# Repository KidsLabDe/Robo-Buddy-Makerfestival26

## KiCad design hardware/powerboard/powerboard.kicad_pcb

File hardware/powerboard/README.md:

# Powerboard (KiCad)

Trägerplatine, die den Robo-Buddy akkubetrieben macht. Anforderungen und Begründungen: `POWERBOARD-HANDOFF.md` im Repo-Hauptordner. ESP-Board: `../esp32-c6-zero/`.

Stand Rev 0.2: **Schaltplan fertig, ERC ohne Meldungen. Platine mit echter Kontur, platziert und geroutet (2 Lagen). Fertigungsdateien für JLCPCB in `fertigung/`. Rev 0.2 ist bestellt, siehe „Bestellung“.**

## Was drauf ist

- Akku (Pouch-LiPo, 1S) an J1, JST-PH **THT**: Verpolschutz (2 × AO3401A parallel), Zellschutz DW01A mit 2 × FS8205A parallel (Auslösung ~6–8 A).
- Strom- und Spannungsmessung: INA226 an I²C (Adresse 0x45), Shunt 10 mΩ zwischen `BAT_CELL` und `BAT+`. Misst Lade- (negativ) und Entladestrom sowie die Akkuspannung.
- Lader TP4056, 235 mA, aus dem 5V-Pin des ESP (USB). Rote LED leuchtet nur beim Laden.
- Ein/Aus (Q5 + SW1) und ideale Diode LM66100 für den ESP.
- 5-V-Servoschiene: Boost TPS61023 (≥ 2 A bei 5 V), von GPIO15 geschaltet. Bei EN low ist der Ausgang echt vom Akku getrennt.
- Ports (alle 2,54 mm, THT-Kit):

| Port | Belegung | GPIO |
|---|---|---|
| Servo 1–4 (J2, J3, J5, J6) | S + − (5 V) | 19, 18, 16, 17 |
| Analog A0–A2 (J7–J9) | GND 3V3 SIG, 1 kΩ in Serie, 0–3,1 V | 0, 1, 2 |
| I²C 1, 2 (J10, J11) | GND 3V3 SDA SCL, 4,7 kΩ Pull-ups | SDA 14, SCL 22 |
| Display (J4) | VCC GND SCL SDA DC CS RST, per Kabel | 4, 5, 20, 21, 3 |

## Platine

`powerboard.kicad_pcb` erzeugt `tools/gen_pcb.py`. Kontur, Platzierung und Herleitung der Maße stehen dort im Kopf.

**Kontur** aus `cad/MF26-Roboter.step`: Innenseite der Hülle direkt über der Bodenplatte, 0,5 mm Luft. Ca. 55 × 53 mm, vorne gerade hinter dem Display, hinten zwei Schrägen und ein gerades Stück vor dem Dom des Schleifrads.

**Platzierung:**
- ESP an der einen hinteren Schräge, USB-C zeigt durch die Wand. Schalter und Lade-LED an der anderen Schräge.
- Servo-Leisten an der einen Längsseite, Analog-Leisten an der anderen, beide ein Stück vom Rand nach innen gesetzt (die Kabel kommen von oben).
- **Leistungsblock vorne**, alles mit festem, breitem Kupfer vorverdrahtet (`POWER_TRACKS` in `gen_pcb.py`):
  - 5-V-Schiene (1,2 mm) direkt hinter den Servo-Leisten, Stich zu jedem Plus-Pin
  - Boost TPS61023 nach dem Layout-Beispiel von TI: Spule direkt über dem SW-Pin, vier Ausgangskondensatoren in einer Spalte zwischen VOUT und GND, Eingangskondensator an VIN
  - Akkupfad J1 → Verpolschutz (Q1, Q7) → Shunt R15 → Spule, Zellschutz Q2/Q6 neben J1
- Display-Leiste J4 ungefähr mittig auf der Displayachse, hinter dem Leistungsblock; zum Display per Kabel.
- I²C-Leisten, Testpunkte und Pull-ups in der Mitte, INA226 hinter dem Shunt.
- Lader und Power Path beim ESP, Ein/Aus-FET direkt hinter dem Schalter.

| Ansicht | Datei |
|---|---|
| Passung im Gehäuse (Schnitte) | `ansichten/passung_schnitte.png`, erzeugt von `tools/render_fit.py` |
| 2D oben / unten | `ansichten/2d_oben.png`, `ansichten/2d_unten.png` |
| 3D oben / unten / schräg | `ansichten/3d_oben.png`, `ansichten/3d_unten.png`, `ansichten/3d_schraeg.png` |

Hinweise:
- **USB-C** endet ca. 1,25 mm hinter der Außenfläche der Hülle. Ganz bündig ginge nur, wenn das ESP-Modul 1 mm über die Platinenkante ragt. Dann läge aber Pad 1 auf der Kante, weil der erste Pin nur 1,6 mm hinter der Modulkante sitzt. Bei Bedarf lässt sich die Wand um die Buchse innen etwas ausdünnen.
- **Display:** Es steht vorne tiefer als die Platine. J4 ist deshalb eine Stiftleiste für ein kurzes Kabel.
- Mindestabstand im Projekt 0,15 mm, minimale Bahnbreite 0,15 mm (Pads des SOT-563 und des INA226 liegen so eng). JLC fertigt 0,1 mm.
- **Drehung bei JLC:** Die Bauteilmodelle von JLC liegen teils anders als die KiCad-Footprints. `tools/export_jlc.py` korrigiert die Drehung in der CPL pro LCSC-Teil (`JLC_ROTATION`): AO3401A, FS8205A, TPS61023 um 180°, DW01A, LM66100, TP4056, INA226 um 90° im Uhrzeigersinn. Am 8. Oktober 2026 im Platzierungs-Viewer von JLC geprüft, Pin 1 jedes Teils sitzt auf der Pin-1-Markierung, D1 mit Kathode an Pin 1. Neue Teile dort prüfen und eintragen.
- Bauteilnummern stehen nicht im Bestückungsdruck, nur auf der Fab-Lage (Bestückung bei JLC geht nach Koordinaten, die Anschlüsse haben eigene Beschriftungen).
- In 3D fehlt das ESP-Modul selbst, weil es dafür kein 3D-Modell gibt. Zu sehen sind nur die beiden Buchsenleisten.

### Öffnungen in der Hülle (CAD-Koordinaten, für FreeCAD)

Platine liegt auf der Bodenplatte, Unterseite z = 12,5, Oberseite z = 14,1.

| Öffnung | Wand | Mitte (x, y) an der Wandaußenseite | Höhe z | Hinweis |
|---|---|---|---|---|
| USB-C | Schräge, niedriges y | (42,2 / 5,2) | ≈ 27–28 | hängt von Leisten- und Modulhöhe ab, am Muster messen; Öffnung für den Stecker ~12,5 × 7 mm |
| Schalterhebel | Schräge, hohes y | (47,6 / 41,7) | ≈ 15,5 | Hebel ragt ~1,4 mm aus der Wand, 2 mm Hub entlang der Wand |
| Lade-LED | Schräge, hohes y | (38,0 / 48,9) | ≈ 14,5 | 0603 strahlt nach oben, sitzt 1 mm vor der Wand: Fenster knapp über der Platine oder Lichtleiter |

## Dateien

| Datei | Inhalt |
|---|---|
| `powerboard.kicad_sch` | Schaltplan, **erzeugt** von `tools/gen_sch.py` |
| `powerboard.kicad_sym` | Projektsymbole FS8205A, TPS61023 und ESP32-C6-Zero, erzeugt von `tools/gen_lib.py` |
| `powerboard.pretty/` | Footprints C6-Zero-Sockel, Shunt mit Kelvin-Pads, Schalter mit runden Pads, KidsLab-Logo; erzeugt von `tools/gen_lib.py` |
| `logo/kidslab-logo.svg` | Vorlage für das Logo auf der Unterseite |
| `powerboard.kicad_pcb` | Platine: Platzierung von `tools/gen_pcb.py`, Leiterbahnen von `tools/route.py` |
| `fertigung/` | JLCPCB: `powerboard_gerber.zip`, `powerboard_bom.csv`, `powerboard_cpl.csv`, erzeugt von `tools/export_jlc.py` |
| `tools/` | Generatoren, Routing (`route.py`, `maze.py`), Ansichten (`render_views.py`, `render_fit.py`) |

Schaltplan und Platine entstehen aus den Skripten. Änderungen also dort machen und neu erzeugen, nicht im Editor:

```
python3 tools/gen_lib.py
python3 tools/gen_sch.py
kicad-cli sch erc powerboard.kicad_sch
python3 tools/gen_pcb.py          # Platzierung + festes Kupfer des Leistungsblocks
python3 tools/route.py            # 20–30 min, siehe unten
kicad-cli pcb drc powerboard.kicad_pcb
python3 tools/render_views.py
python3 tools/render_fit.py
python3 tools/export_jlc.py
```

### Routing

`tools/route.py` braucht [Freerouting](https://github.com/freerouting/freerouting) 2.4.1 als `~/.cache/freerouting/freerouting-2.4.1.jar` (oder `$FREEROUTING_JAR`) und Java.

1. Kurze Verbindungen an der Kante (Schalter, LED, ESP-Pin 1) und in manchen Varianten die Leistungsnetze werden zuerst allein geroutet und gesperrt, danach alles andere.
2. Freerouting kommt mit zwei Dingen dieser Platine nicht zurecht, `route.py` umgeht beide in der Exportdatei:
   - **Schräge Bauteile:** Pads von Bauteilen unter 126,5° bzw. 53,5° (ESP, Schalter) sind für Freerouting nicht erreichbar. Die Drehung wird deshalb in die Pad-Positionen eingerechnet.
   - **Schräge Kanten:** Pads bis ~2 mm vor den schrägen Kanten sind ebenfalls unerreichbar. Die Kontur wird deshalb durch das umschließende Rechteck plus Sperrflächen ersetzt.
3. Acht Varianten (Reihenfolge, Bahnbreite, Durchläufe), die mit den wenigsten offenen Verbindungen bleibt.
4. `tools/maze.py` schließt, was noch offen ist (Raster-Router, 0,1 mm, mit Lagenwechsel).
5. Leistungsbahnen so breit wie der DRC erlaubt (bis 1,2 mm), GND-Fläche oben und unten mit Durchkontaktierungen, hängende Vias weg.

GND wird wie ein normales Netz geroutet; die Flächen verstärken es nur. So bleibt GND verbunden, auch wenn Signale eine Fläche zerschneiden.

## Prüfungen

- `kicad-cli sch erc`: 0 Meldungen.
- Netzliste geprüft:
  - `BATN` nur an J1.2, DW01 VSS, S1 beider FS8205A, R1, C1
  - `V5_SERVO` nur an Servo-Plus, Boost-Ausgang, Rückkopplung, Ausgangskondensatoren und TP4
  - kein Servo-Plus an `3V3` oder `VSYS`
  - Shunt R15 zwischen `BAT_CELL` (INA226 IN+) und `BAT+` (IN−, VBUS)
  - GPIOs wie oben
- Pinbelegungen aus den Datenblättern:
  - FS8205A (C908265): 1 S1, 2 D, 3 S2, 4 G2, 5 D, 6 G1
  - DW01A (C2927799): 1 OD, 2 CS, 3 OC, 4 NC, 5 VDD, 6 VSS
  - TP4056 (C16581): 1 TEMP, 2 PROG, 3 GND, 4 VCC, 5 BAT, 6 STDBY, 7 CHRG, 8 CE, EP GND. KiCad-Symbol `TP4056-42-ESOP8`, das genau dieses Teil ist.
  - TPS61023 (C919459, TI SLVSF14B): 1 FB, 2 EN, 3 VIN, 4 GND, 5 SW, 6 VOUT. V_REF 0,595 V, mit 750 k / 100 k → 5,06 V.
  - INA226 (C49851): 1 A1, 2 A0, 3 ALERT, 4 SDA, 5 SCL, 6 VS, 7 GND, 8 VBUS, 9 IN−, 10 IN+
  - LM66100: 1 VIN, 2 GND, 3 CE, 4 NC, 5 ST, 6 VOUT
- Das LM66100-Datenblatt empfiehlt, ST auf GND zu legen, wenn es nicht gebraucht wird. Hier ist es offen gelassen: Es ist ein Open-Drain-Ausgang, und auf GND gelegt würde ERC einen Typkonflikt mit dem PWR_FLAG melden. Elektrisch macht das keinen Unterschied.

## Bestellung

Rev 0.2 am 8. Oktober 2026 bei JLCPCB in den Warenkorb gelegt (noch nicht bezahlt):

- PCB: 10 Stück, FR-4, 2 Lagen, 1,6 mm, grün, **LeadFree HASL** (die Kinder löten die THT-Teile selbst), 54,8 × 53,2 mm laut JLC.
- PCBA: Economic, nur Oberseite, 10 Stück, alle 24 Positionen automatisch zugeordnet, ohne THT-Teile.
- Produktbeschreibung für den Zoll: Research/Education/DIY, „DIY“ (HS 902300).
- Preis: 6,20 $ PCB + 67,81 $ PCBA = 74,01 $ ohne Versand (Bauteile 34,10 $, Extended-Gebühr 21,63 $).

## Offen

- **Akkuwiege in der Hülle:** Die Hülle hat noch die Wiege für den Zylinder-Akku (Wände bei y ≈ 17 und 34, ab z ≈ 22). Die hintere Ecke des gesteckten ESP ragt da hinein (`passung_schnitte.png`, rechtes Bild). Für den Pouch-Akku muss die Wiege ohnehin raus.
- **Befestigung:** H1 und H2 (M2) bleiben, wo sie sind. Die Bodenplatte (3D-Druck) wird bei Bedarf an die Platine angepasst.
- **Footprint C6-Zero:** Reihenabstand 15,24 mm (6 × 2,54) laut Waveshare-DXF, Wert in `tools/gen_lib.py` (`ROW`).
- **SW1:** CK OS102011MA1Q, gewinkelt.
- **Strom:** JST-PH ist für 2 A spezifiziert. Im Betrieb reicht das, blockieren alle 4 Servos, sind kurz 3–4 A möglich. Die Zelle muss diese Spitzen liefern können.
- **INA226 bei ausgeschaltetem ESP:** Die Messeingänge hängen am Akku, die Versorgung (3V3) fehlt dann. Laut Datenblatt sind die Eingänge unabhängig von VS bis 36 V zulässig. Den Ruhestrom im ausgeschalteten Zustand am Prototyp messen.
- **THT-Teile:** U4-Sockel, J1–J11 und SW1 sind mit dem Feld `Kit = THT-Kit` markiert. Beim JLC-Export werden sie herausgefiltert.

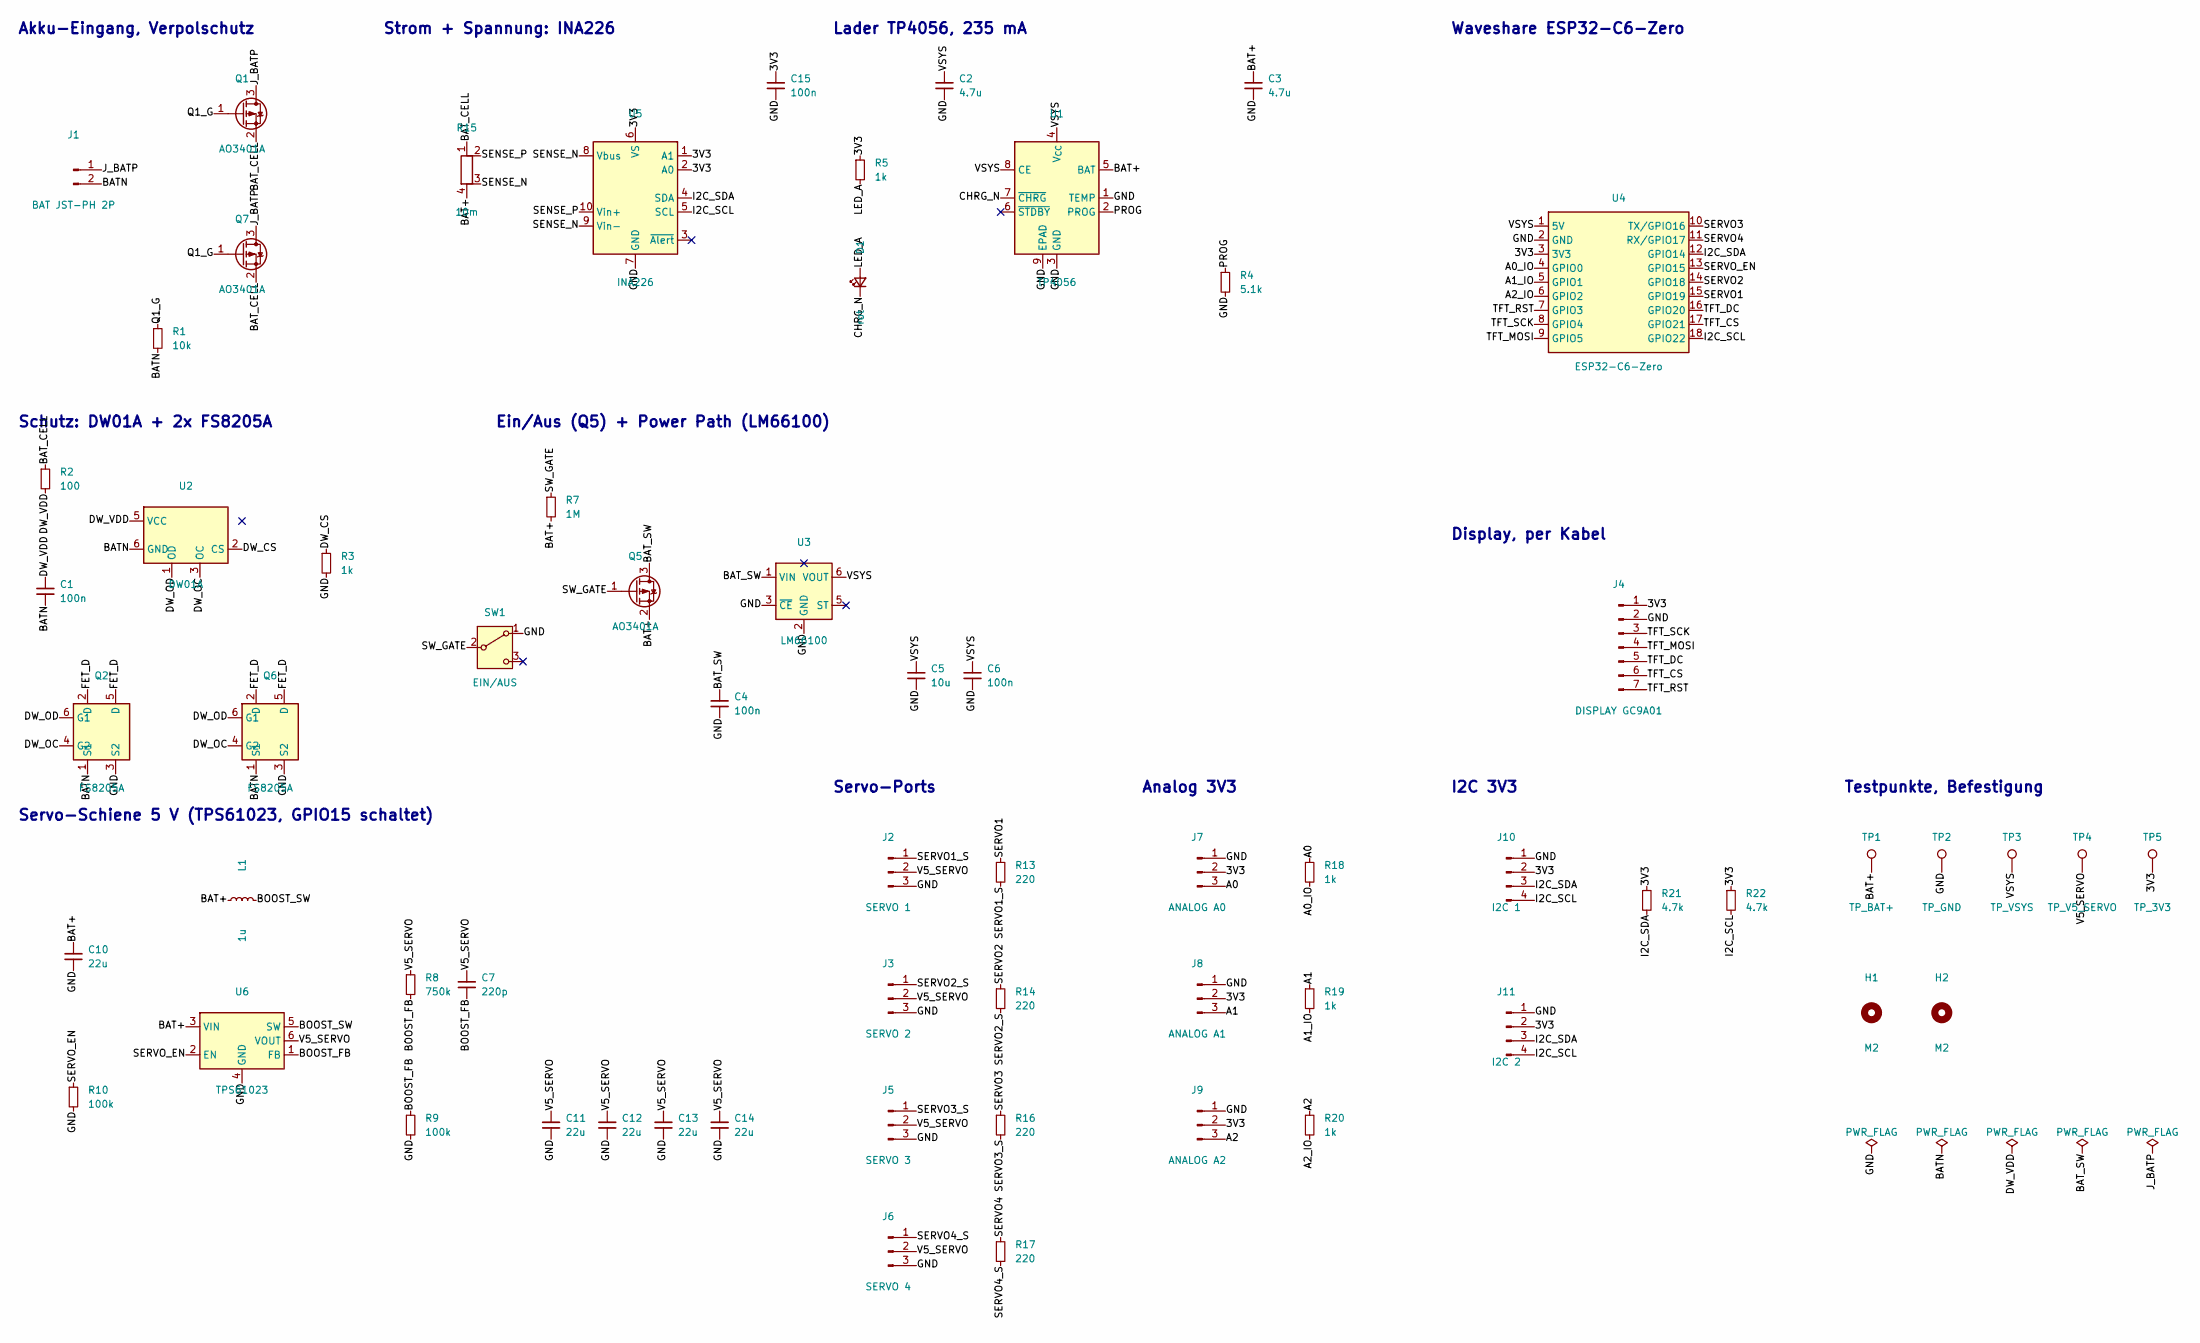
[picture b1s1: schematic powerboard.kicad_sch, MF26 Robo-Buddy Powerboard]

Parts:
C1, C4, C6, C15: 100n; C_0603_1608Metric; LCSC C14663
C2, C3: 4.7u; C_0805_2012Metric; LCSC C1779
C5: 10u; C_0805_2012Metric; LCSC C15850
C7: 220p; C_0603_1608Metric; LCSC C1603
C10, C11, C12, C13, C14: 22u; C_0805_2012Metric; LCSC C45783
D1: rot; LED_0603_1608Metric; LCSC C2286
H1, H2: M2; MountingHole_2.2mm_M2
J1: BAT JST-PH 2P; JST_PH_B2B-PH-K_1x02_P2.00mm_Vertical
J2: SERVO 1; PinHeader_1x03_P2.54mm_Vertical
J3: SERVO 2; PinHeader_1x03_P2.54mm_Vertical
J4: DISPLAY GC9A01; PinHeader_1x07_P2.54mm_Vertical
J5: SERVO 3; PinHeader_1x03_P2.54mm_Vertical
J6: SERVO 4; PinHeader_1x03_P2.54mm_Vertical
J7: ANALOG A0; PinHeader_1x03_P2.54mm_Vertical
J8: ANALOG A1; PinHeader_1x03_P2.54mm_Vertical
J9: ANALOG A2; PinHeader_1x03_P2.54mm_Vertical
J10: I2C 1; PinHeader_1x04_P2.54mm_Vertical
J11: I2C 2; PinHeader_1x04_P2.54mm_Vertical
L1: 1u; L_Sunlord_MWSA0402S; LCSC C408332
Q1, Q5, Q7: AO3401A; SOT-23; LCSC C15127
Q2, Q6: FS8205A; SOT-23-6; LCSC C908265
R1: 10k; R_0603_1608Metric; LCSC C25804
R2: 100; R_0603_1608Metric; LCSC C22775
R3, R5, R18, R19, R20: 1k; R_0603_1608Metric; LCSC C21190
R4: 5.1k; R_0603_1608Metric; LCSC C23186
R7: 1M; R_0603_1608Metric; LCSC C22935
R8: 750k; R_0603_1608Metric; LCSC C23240
R9, R10: 100k; R_0603_1608Metric; LCSC C25803
R13, R14, R16, R17: 220; R_0603_1608Metric; LCSC C22962
R15: 10m; R_1206_3216Metric_Kelvin; LCSC C105362
R21, R22: 4.7k; R_0603_1608Metric; LCSC C23162
SW1: EIN/AUS; SW_Slide_SPDT_Angled_CK_OS102011MA1Q_Round
TP1: TP_BAT+; TestPoint_Pad_D1.0mm
TP2: TP_GND; TestPoint_Pad_D1.0mm
TP3: TP_VSYS; TestPoint_Pad_D1.0mm
TP4: TP_V5_SERVO; TestPoint_Pad_D1.0mm
TP5: TP_3V3; TestPoint_Pad_D1.0mm
U1: TP4056; SOIC-8-1EP_3.9x4.9mm_P1.27mm_EP2.41x3.3mm; LCSC C16581
U2: DW01A; SOT-23-6; LCSC C2927799
U3: LM66100; SOT-363_SC-70-6; LCSC C2869734
U4: ESP32-C6-Zero; Waveshare_ESP32-C6-Zero_Socket
U5: INA226; TSSOP-10_3x3mm_P0.5mm; LCSC C49851
U6: TPS61023; SOT-563; LCSC C919459

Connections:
/3V3: C15.1, J4.1, J7.2, J8.2, J9.2, J10.2, J11.2, R5.1, R21.1, R22.1, TP5.1, U4.3 (3V3), U5.1 (A1), U5.2 (A0), U5.6 (VS)
/A0: J7.3, R18.1
/A0_IO: R18.2, U4.4 (GPIO0)
/A1: J8.3, R19.1
/A1_IO: R19.2, U4.5 (GPIO1)
/A2: J9.3, R20.1
/A2_IO: R20.2, U4.6 (GPIO2)
/BAT+: C3.1, C10.1, L1.1, Q5.2 (S), R7.2, R15.4, TP1.1, U1.5 (BAT), U6.3 (VIN)
/BATN: C1.2, J1.2, Q2.1 (S1), Q6.1 (S1), R1.2, U2.6 (GND)
/BAT_CELL: Q1.2 (S), Q7.2 (S), R2.1, R15.1
/BAT_SW: C4.1, Q5.3 (D), U3.1 (VIN)
/BOOST_FB: C7.2, R8.2, R9.1, U6.1 (FB)
/BOOST_SW: L1.2, U6.5 (SW)
/CHRG_N: D1.1 (K), U1.7 (~CHRG)
/DW_CS: R3.1, U2.2 (CS)
/DW_OC: Q2.4 (G2), Q6.4 (G2), U2.3 (OC)
/DW_OD: Q2.6 (G1), Q6.6 (G1), U2.1 (OD)
/DW_VDD: C1.1, R2.2, U2.5 (VCC)
/FET_D: Q2.2 (D), Q2.5 (D), Q6.2 (D), Q6.5 (D)
/GND: C2.2, C3.2, C4.2, C5.2, C6.2, C10.2, C11.2, C12.2, C13.2, C14.2, C15.2, J2.3, J3.3, J4.2, J5.3, J6.3, J7.1, J8.1, J9.1, J10.1, J11.1, Q2.3 (S2), Q6.3 (S2), R3.2, R4.2, R9.2, R10.2, SW1.1 (A), TP2.1, U1.1 (TEMP), U1.3 (GND), U1.9 (EPAD), U3.2 (GND), U3.3 (~CE), U4.2 (GND), U5.7 (GND), U6.4 (GND)
/I2C_SCL: J10.4, J11.4, R22.2, U4.18 (GPIO22), U5.5 (SCL)
/I2C_SDA: J10.3, J11.3, R21.2, U4.12 (GPIO14), U5.4 (SDA)
/J_BATP: J1.1, Q1.3 (D), Q7.3 (D)
/LED_A: D1.2 (A), R5.2
/PROG: R4.1, U1.2 (PROG)
/Q1_G: Q1.1 (G), Q7.1 (G), R1.1
/SENSE_N: R15.3, U5.8 (Vbus), U5.9 (Vin-)
/SENSE_P: R15.2, U5.10 (Vin+)
/SERVO1: R13.1, U4.15 (GPIO19)
/SERVO1_S: J2.1, R13.2
/SERVO2: R14.1, U4.14 (GPIO18)
/SERVO2_S: J3.1, R14.2
/SERVO3: R16.1, U4.10 (TX/GPIO16)
/SERVO3_S: J5.1, R16.2
/SERVO4: R17.1, U4.11 (RX/GPIO17)
/SERVO4_S: J6.1, R17.2
/SERVO_EN: R10.1, U4.13 (GPIO15), U6.2 (EN)
/SW_GATE: Q5.1 (G), R7.1, SW1.2 (B)
/TFT_CS: J4.6, U4.17 (GPIO21)
/TFT_DC: J4.5, U4.16 (GPIO20)
/TFT_MOSI: J4.4, U4.9 (GPIO5)
/TFT_RST: J4.7, U4.7 (GPIO3)
/TFT_SCK: J4.3, U4.8 (GPIO4)
/V5_SERVO: C7.1, C11.1, C12.1, C13.1, C14.1, J2.2, J3.2, J5.2, J6.2, R8.1, TP4.1, U6.6 (VOUT)
/VSYS: C2.1, C5.1, C6.1, TP3.1, U1.4 (V_{CC}), U1.8 (CE), U3.6 (VOUT), U4.1 (5V)

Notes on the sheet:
Akku-Eingang, Verpolschutz
Schutz: DW01A + 2x FS8205A
Strom + Spannung: INA226
Lader TP4056, 235 mA
Ein/Aus (Q5) + Power Path (LM66100)
Servo-Schiene 5 V (TPS61023, GPIO15 schaltet)
Servo-Ports
Analog 3V3
I2C 3V3
Waveshare ESP32-C6-Zero
Display, per Kabel
Testpunkte, Befestigung

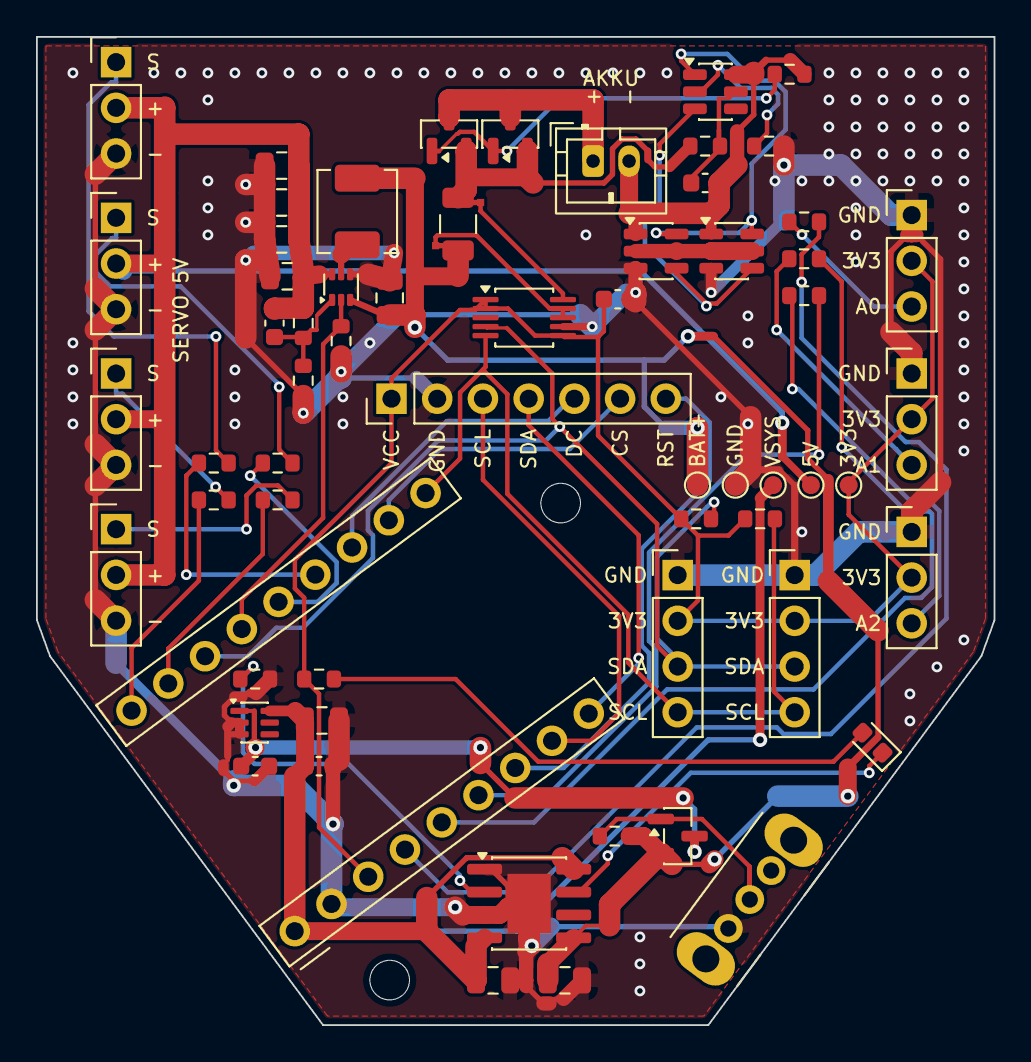
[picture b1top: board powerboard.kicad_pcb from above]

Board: 2 copper layers, 53.2 x 54.9 mm, 65 parts (1 on the bottom side), 45 nets.

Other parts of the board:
LOGO1: KidsLab_Logo

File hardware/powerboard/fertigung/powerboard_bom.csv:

Comment,Designator,Footprint,LCSC
100n,"C1,C4,C6,C15",C_0603_1608Metric,C14663
4.7u,"C2,C3",C_0805_2012Metric,C1779
10u,C5,C_0805_2012Metric,C15850
220p,C7,C_0603_1608Metric,C1603
22u,"C10,C11,C12,C13,C14",C_0805_2012Metric,C45783
rot,D1,LED_0603_1608Metric,C2286
1u,L1,L_Sunlord_MWSA0402S,C408332
AO3401A,"Q1,Q5,Q7",SOT-23,C15127
FS8205A,"Q2,Q6",SOT-23-6,C908265
10k,R1,R_0603_1608Metric,C25804
100,R2,R_0603_1608Metric,C22775
1k,"R3,R5,R18,R19,R20",R_0603_1608Metric,C21190
5.1k,R4,R_0603_1608Metric,C23186
1M,R7,R_0603_1608Metric,C22935
750k,R8,R_0603_1608Metric,C23240
100k,"R9,R10",R_0603_1608Metric,C25803
220,"R13,R14,R16,R17",R_0603_1608Metric,C22962
10m,R15,R_1206_3216Metric_Kelvin,C105362
4.7k,"R21,R22",R_0603_1608Metric,C23162
TP4056,U1,SOIC-8-1EP_3.9x4.9mm_P1.27mm_EP2.41x3.3mm,C16581
DW01A,U2,SOT-23-6,C2927799
LM66100,U3,SOT-363_SC-70-6,C2869734
INA226,U5,TSSOP-10_3x3mm_P0.5mm,C49851
TPS61023,U6,SOT-563,C919459

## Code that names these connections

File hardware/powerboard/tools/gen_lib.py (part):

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                  (-7.62, 5.08, 7.62, -5.08), pins)


LEFT = ['5V','GND', '3V3', 'GPIO0', 'GPIO1', 'GPIO2', 'GPIO3', 'GPIO4', 'GPIO5']
RIGHT = ['TX/GPIO16', 'RX/GPIO17', 'GPIO14', 'GPIO15', 'GPIO18', 'GPIO19', 'GPIO20', 'GPIO21', 'GPIO22']
KIND = {'5V': 'power_in', 'GND': 'power_in', '3V3': 'power_out'}


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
